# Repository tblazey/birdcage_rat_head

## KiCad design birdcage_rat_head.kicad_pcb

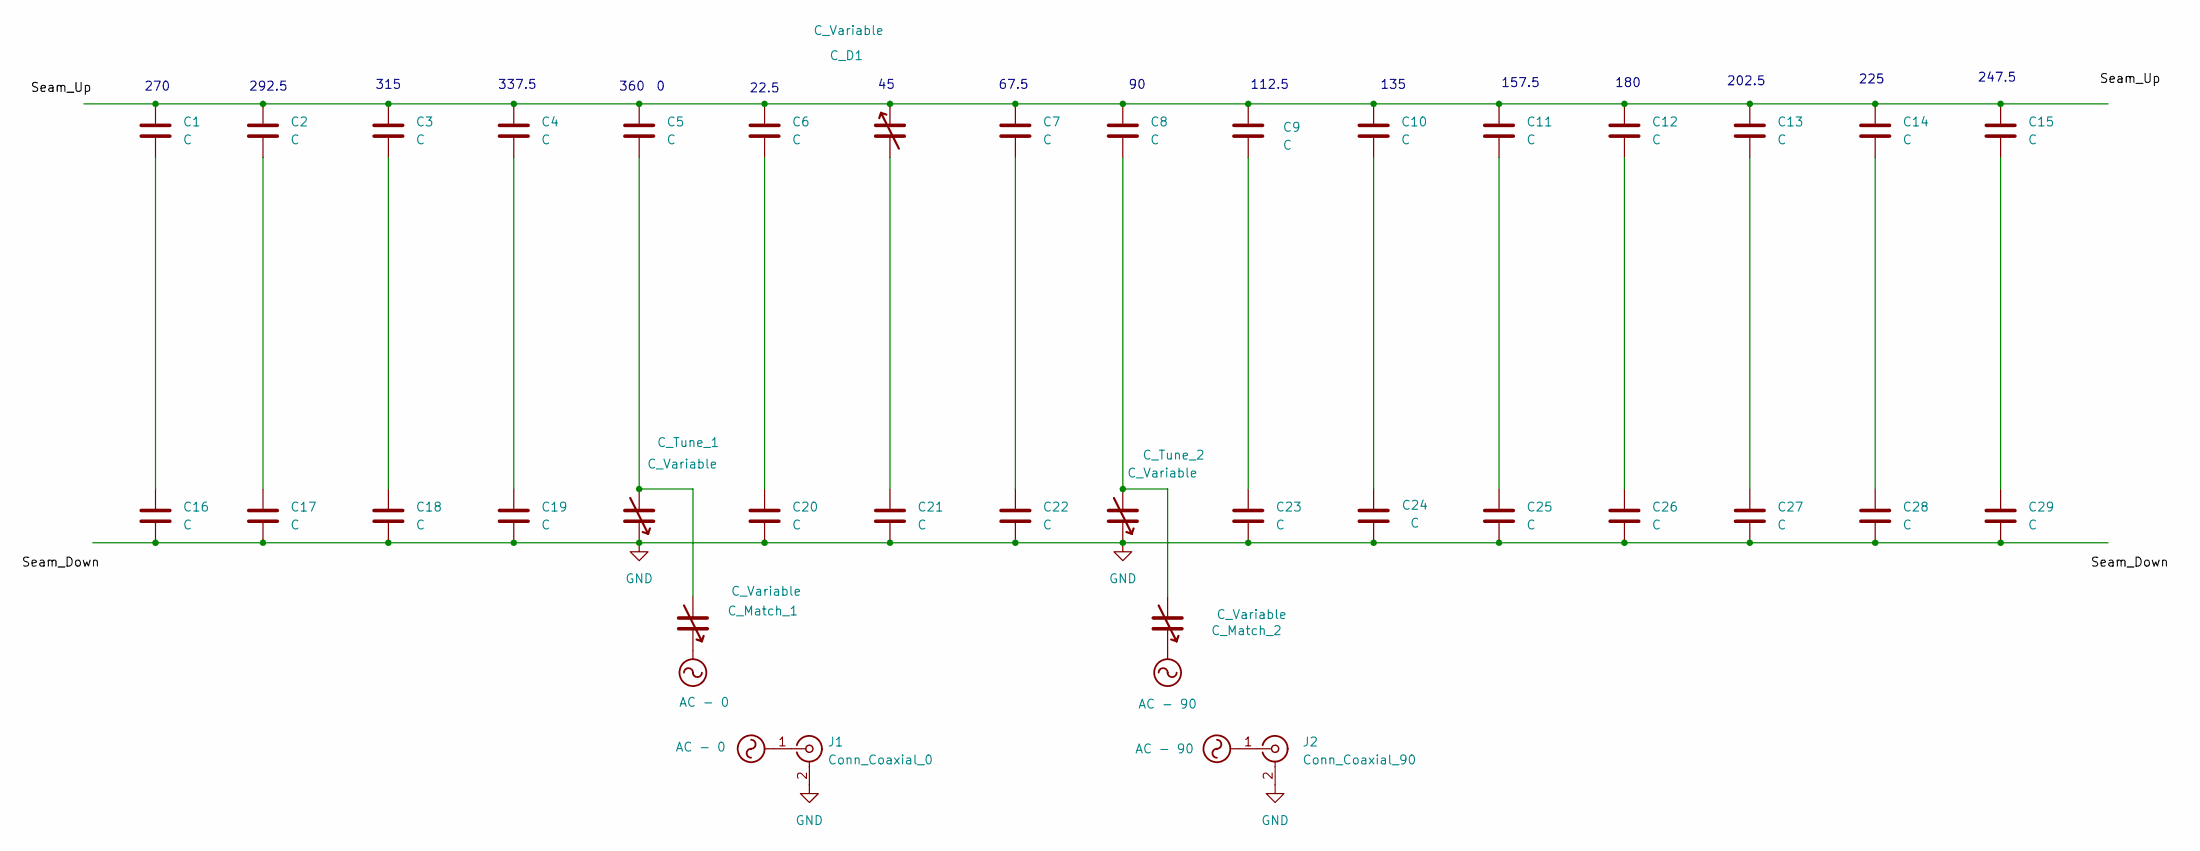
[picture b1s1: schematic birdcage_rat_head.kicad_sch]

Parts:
C1, C2, C3, C4, C5, C6, C7, C8, C9, C10, C11, C12, C13, C14, C15, C16, C17, C18, C19, C20, C21, C22, C23, C24, C25, C26, C27, C28, C29: C; CAP_R07_AV4T_JOD
C_D1: C_Variable; trimmer_cap_tiny
C_Match_1, C_Match_2: C_Variable; trimmer_cap_smaller
C_Tune_1, C_Tune_2: C_Variable; trimmer_cap_smaller
J1: Conn_Coaxial_0; 142-9701-301
J2: Conn_Coaxial_90; 142-9701-301

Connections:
AC - 0: C_Match_1.1, J1.1 (In)
AC - 90: C_Match_2.1, J2.1 (In)
GND: C16.1, C17.1, C18.1, C19.1, C20.1, C21.1, C22.1, C23.1, C24.1, C25.1, C26.1, C27.1, C28.1, C29.1, C_Tune_1.1, C_Tune_2.1, J1.2 (Ext), J2.2 (Ext)
unnamed: C1.1, C16.2
unnamed: C1.2, C2.2, C3.2, C4.2, C5.2, C6.2, C7.2, C8.2, C9.2, C10.2, C11.2, C12.2, C13.2, C14.2, C15.2, C_D1.1
unnamed: C5.1, C_Match_1.2, C_Tune_1.2
unnamed: C8.1, C_Match_2.2, C_Tune_2.2
unnamed: C10.1, C24.2
unnamed: C11.1, C25.2
unnamed: C12.1, C26.2
unnamed: C13.1, C27.2
unnamed: C14.1, C28.2
unnamed: C15.1, C29.2
unnamed: C2.1, C17.2
unnamed: C3.1, C18.2
unnamed: C4.1, C19.2
unnamed: C6.1, C20.2
unnamed: C21.2, C_D1.2
unnamed: C7.1, C22.2
unnamed: C9.1, C23.2

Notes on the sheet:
22.5
315
202.5
247.5
157.5
225
135
292.5
360
337.5
180
270
67.5
112.5

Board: 2 copper layers, 36 parts (0 on the bottom side), 20 nets, no tracks yet.

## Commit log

2025-11-17 Added 3D models
2025-11-17 Accounted for PCB thickness and reduced gap between flange and pcb
    Gap was reduced so that more of the rat brain is in the coil.
2025-11-24 First printing
2025-11-24 Gerbers for first print
